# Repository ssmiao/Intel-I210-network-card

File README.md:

# Intel-I210-network-card
This is a standard PCIe x1 Ethernet Card designed by KiCad.

Before you make it and want to use in your computer, remember to go to DOS system and flash config file to the card. The following steps maybe help.

1. Download [This folder](https://github.com/ssmiao/Intel-I210-network-card)  

2. Use Rufus to create a FreeDOS USB disk (RuFus support itself, you don't need to download a ISO file or something).
3. Copy my folder to the disk.
4. Shutdown the computer and insert the network card
5. Start the computer into FreeDOS system.
6. Go to /FARTHING and run AUTO.BAT

Good luck since I design it 1 year ago and can't remember it clearly. But the hardware can work.

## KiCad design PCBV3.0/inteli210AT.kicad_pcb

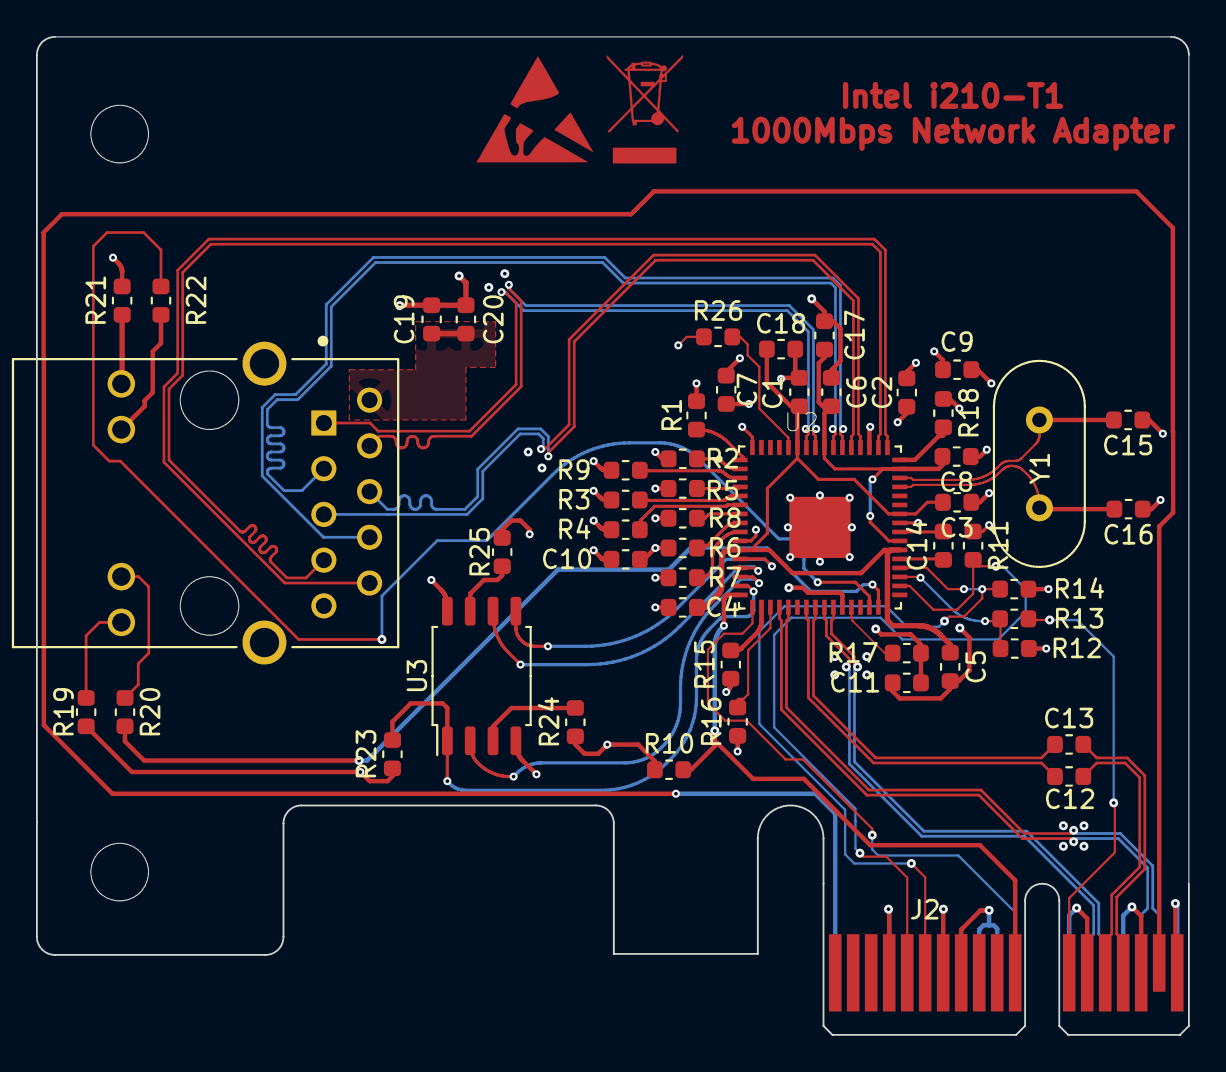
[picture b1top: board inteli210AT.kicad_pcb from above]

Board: 4 copper layers, 64.0 x 55.4 mm, 56 parts (0 on the bottom side), 58 nets.

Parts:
C1, C2, C3, C4, C5, C6, C7, C8, C9, C10, C11, C12, C13, C19, C20: 100nF; C_0603_1608Metric
C14: 39nF; C_0603_1608Metric
C15, C16: 27pF; C_0603_1608Metric
C17, C18: 15uF; C_0603_1608Metric
H1: PCI-baffle; i210-pcibaffle
J1: HR911130C; HANRUN_HR911130C
J2: PCIe-x1; BUS_PCIexpress_x1
Logo1, Logo1#2: Logo; WEEE-Logo_4.2x6mm_SilkScreen
Logo2, Logo2#2: Logo; ESD-Logo_6.6x6mm_SilkScreen
R1: 3.3k; R_0603_1608Metric
R2, R8, R9: 10K; R_0603_1608Metric
R3, R4, R6, R7, R12, R17, R26: 10k; R_0603_1608Metric
R5, R15, R16: 3.3K; R_0603_1608Metric
R10, R11, R13, R14: NULL; R_0603_1608Metric
R18: 4.99k 1%; R_0603_1608Metric
R19, R20, R21, R22: 160R; R_0603_1608Metric
R23, R24, R25: 5k; R_0603_1608Metric
U2: i210; QFN50P900X900X100-65N
U3: W25Q16; SOIC-8_5.23x5.23mm_P1.27mm
Y1: 25MHz; Crystal_HC49-4H_Vertical

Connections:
+3V3: C2.2, C7.2, C9.2, C10.2, C11.2, J2.A9, J2.A10, J2.B8, R1.1, R3.1, R4.1, R5.1, R6.1, R7.1, R10.1, R11.1, R12.1, R14.1, R15.1, R16.1, R17.1, R19.2, R21.2, R23.1, R24.1, R25.1, U2.10, U2.27, U2.41, U2.51, U2.64, U3.8
/0V9: C1.2, C3.2, C4.2, C5.2, C18.2, U2.11, U2.32, U2.38, U2.42, U2.59
/1V5: C6.2, C8.2, C17.2, U2.39, U2.47, U2.56
/CLKREQ#: J2.B12, R13.1
/DEV_OFF_N: R17.2, U2.28
/JTAG_CLK: R16.2, U2.19
/JTAG_TDO: R5.2, U2.4
/JTAG_TMS: R15.2, U2.18
/LAN_PWR_GOOD: R1.2, U2.1
/LED0: R20.2, U2.31
/LED1: R22.2, U2.30
/MDI0+: J1.2, U2.58
/MDI0-: J1.3, U2.57
/MDI1+: J1.4, U2.55
/MDI1-: J1.7, U2.54
/MDI2+: J1.5, U2.53
/MDI2-: J1.6, U2.52
/MDI3+: J1.8, U2.50
/MDI3-: J1.9, U2.49
/NC_SI_CLK_IN: R2.2, U2.2
/NC_SI_CRS_DV: R9.2, U2.3
/NC_SI_RXD0: R4.2, U2.6
/NC_SI_RXD1: R3.2, U2.5
/NC_SI_TXD0: R7.2, U2.9
/NC_SI_TXD1: R6.2, U2.8
/NC_SI_TX_EN: R8.2, U2.7
/NVM_CS_N: R23.2, U2.15, U3.1
/NVM_SI: U2.12, U3.5
/NVM_SK: U2.13, U3.6
/NVM_SO: U2.14, U3.2
/PECLK+: J2.A14, U2.26
/PECLK-: J2.A13, U2.25
/PERST#: J2.A11, U2.17
/PE_R+: J2.A17, U2.21
/PE_R-: J2.A16, U2.20
/PE_T+: C12.2, J2.B14
/PE_T-: C13.2, J2.B15
/PE_T_N: C12.1, U2.23
/PE_T_P: C13.1, U2.24
/PRSNT1#: J2.A1, J2.B17
/SMB+: J2.B6, R14.2, U2.36
/SMB-: J2.B5, R11.2, U2.34
/SMB_ALRT_N: R12.2, R13.2, U2.35
/WAKE#: J2.B11, R10.2, U2.16
/XTAL+: C15.2, U2.46, Y1.1
/XTAL-: C16.2, U2.45, Y1.2
GND: C1.1, C2.1, C3.1, C4.1, C5.1, C6.1, C7.1, C8.1, C9.1, C10.1, C11.1, C15.1, C16.1, C17.1, C18.1, C19.1, C20.1, J1.10, J1.15, J1.16, J2.A4, J2.A12, J2.A15, J2.A18, J2.B4, J2.B7, J2.B13, J2.B16, J2.B18, R2.1, R8.1, R9.1, R18.1, R26.1, U2.65, U3.4
unnamed: C14.1, U2.37
unnamed: C14.2, U2.40
unnamed: C19.2, C20.2, J1.1
unnamed: J1.11, R21.1
unnamed: J1.12, R22.1
unnamed: J1.13, R20.1
unnamed: J1.14, R19.1
unnamed: R18.2, U2.48
unnamed: R24.2, U3.3
unnamed: R25.2, U3.7
unnamed: R26.2, U2.60

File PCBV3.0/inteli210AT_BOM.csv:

"Comment","Description","Designator","Footprint","LibRef","Pins","Quantity","PartNumber","url",
"100nF","desc","C13,C12,C11,C10,C9,C8,C7,C6,C5,C4,C3,C2,C1,","C_0603_1608Metric","libref","2","13","","",
"39nF","desc","C14,","C_0603_1608Metric","libref","2","1","","",
"27pF","desc","C16,C15,","C_0603_1608Metric","libref","2","2","","",
"15uF","desc","C18,C17,","C_0603_1608Metric","libref","2","2","","",
"3.3k","desc","R1,","R_0603_1608Metric","libref","2","1","","",
"NULL","desc","R14,R13,R11,R10,","R_0603_1608Metric","libref","2","4","","",
"3.3K","desc","R16,R15,R5,","R_0603_1608Metric","libref","2","3","","",
"10k","desc","R17,R12,R7,R6,R4,R3,","R_0603_1608Metric","libref","2","6","","",
"4.99k 1%","desc","R18,","R_0603_1608Metric","libref","2","1","","",
"160R","desc","R22,R21,R20,R19,","R_0603_1608Metric","libref","2","4","","",
"10K","desc","R9,R8,R2,","R_0603_1608Metric","libref","2","3","","",
"i210","desc","U2,","QFN50P900X900X100-65N","libref","65","1","","",
"W25Q16","desc","U3,","SOIC-8_5.23x5.23mm_P1.27mm","libref","8","1","","",
"Through Hole Items ",
"PCI-baffle","desc","H1,","i210-pcibaffle","libref","2","1","","",
"HR911130C","desc","J1,","HANRUN_HR911130C","libref","18","1","","",
"PCIe-x1","desc","J2,","BUS_PCIexpress_x1","libref","36","1","","",
"25MHz","desc","Y1,","Crystal_HC49-4H_Vertical","libref","2","1","","",

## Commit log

2021-03-26 add README file
